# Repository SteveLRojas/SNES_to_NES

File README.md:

# SNES_to_NES
This project is an adapter board designed to be installed inside a SNES gamepad.  
The source is written in assembly for the AT90S1200 MCU. All code is in the main ASM file.  
All the project details can be inferred from the source file, which is short, simple, and well commented.  
A single layer PCB design is included.  

Bug fix: added temporary nes variable in main. This is need so that the NES variable is always valid, as the NES console can trigger an interrupt and read it at any time.  
	In previous versions the A and B buttons had a small chance of getting pressed at random, which made games such as B-Wings effectively unplayable.  

News update: The AT90S1200 microcontroller used in this project has been obsolete for a very long time (~2004), so I will no longer maintain this project.
A new project has been created using an ATtiny24.

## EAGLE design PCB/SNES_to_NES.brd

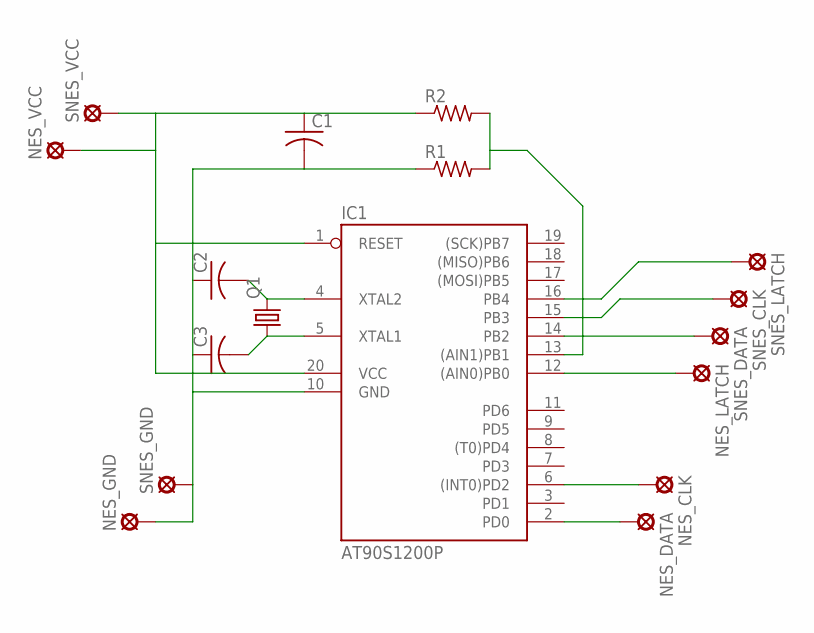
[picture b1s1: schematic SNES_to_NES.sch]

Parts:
C1: C-US025_050-035X075; C025_050-035X075
C2, C3: C-US025-030X050; C025-030X050
IC1: AT90S1200P; DIL20
NES_CLK: MCS08
NES_DATA: MCS08
NES_GND: MCS08
NES_LATCH: MCS08
NES_VCC: MCS08
Q1: CRYSTALHC49U-H; HC49U-H
R1, R2: R-US_0207/7; 0207/7
SNES_CLK: MCS08
SNES_DATA: MCS08
SNES_GND: MCS08
SNES_LATCH: MCS08
SNES_VCC: MCS08

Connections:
GND: C1.2, C2.1, C3.1, IC1.10 (GND), NES_GND.MP, R1.1, SNES_GND.MP
unnamed: C1.1, IC1.1 (RESET), IC1.20 (VCC), NES_VCC.MP, R2.1, SNES_VCC.MP
unnamed: IC1.15 (PB3), SNES_CLK.MP
unnamed: C3.2, IC1.5 (XTAL1), Q1.1
unnamed: C2.2, IC1.4 (XTAL2), Q1.2
unnamed: IC1.13 ((AIN1)PB1), R1.2, R2.2
unnamed: IC1.16 (PB4), SNES_LATCH.MP
unnamed: IC1.12 ((AIN0)PB0), NES_LATCH.MP
unnamed: IC1.14 (PB2), SNES_DATA.MP
unnamed: IC1.2 (PD0), NES_DATA.MP
unnamed: IC1.6 ((INT0)PD2), NES_CLK.MP

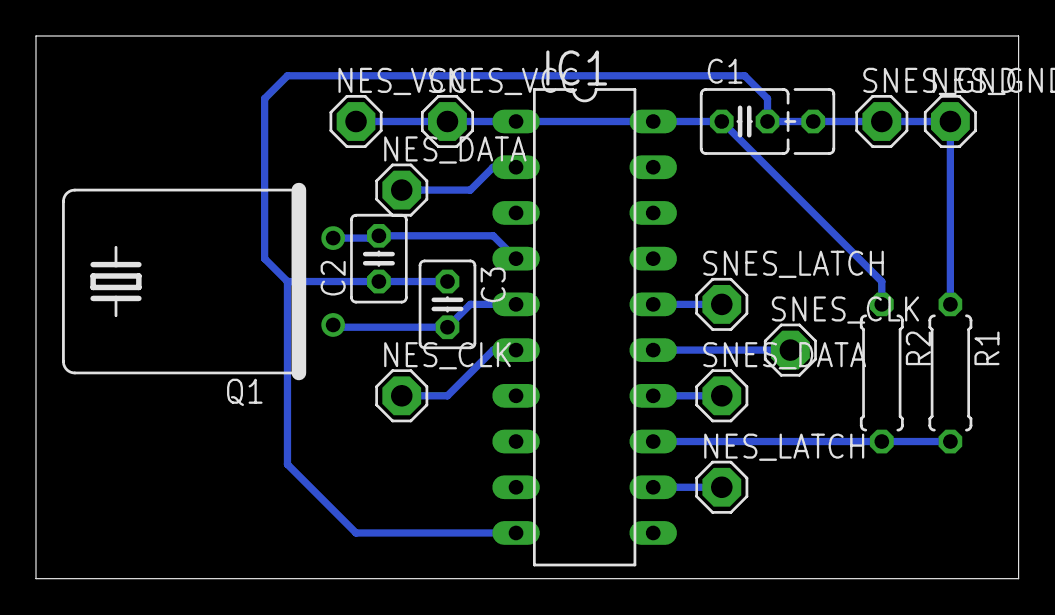
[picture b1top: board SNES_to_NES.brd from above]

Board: 2 copper layers, 54.6 x 30.1 mm, 17 parts (0 on the bottom side), 11 nets.

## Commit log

2020-04-16 bug fix
2020-10-20 Added PCB files
